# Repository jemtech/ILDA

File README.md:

# ILDA
This project is a DAC ([digital to analog converter](https://en.wikipedia.org/wiki/Digital-to-analog_converter)) which generates six [differential signals](https://en.wikipedia.org/wiki/Differential_signaling) based on the ILDA ([International Laser Display Association](http://www.laserist.org/)) [ISP-DB25 standard](http://www.laserist.org/StandardsDocs/ILDA_ISP99_rev002.pdf).
Two signals for the X and Y axis (-10V to +10V), four signals for the channels red, green and blue and one custom colour (0V to +5V).
The DAC is controlled via [SPI](https://en.wikipedia.org/wiki/Serial_Peripheral_Interface_Bus). In this case the software is written for a "Raspberry Pi", but any other controller can be used.

This project contains two sections:

1. Hardware: In this section you find a 16bit 6ch DAC for ILDA. Reaching 22kpps (measured with [ILDA Test Pattern](http://www.laserist.org/StandardsDocs/ILDA_TestPattern95_rev002.pdf), theoretical up to 400kpps) limited by the controling "Raspberry Pi". It is resulting in a resolution of 4294967296 positions (~4295 megapixels).
The asynchronous LDAC update pin at the DAC, immediately updates the DAC register with the contents of the input register, so all outputs change at the same time and can be synchronised with an external clock.
2. Software: C based software to control the ILDA-DAC with a "Raspberry Pi". Supports all Files based on the [ILDA Image Data Transfer Format](http://www.laserist.org/StandardsDocs/ILDA_IDTF14_rev011.pdf).

## Hardware
The hardware is designed with [KiCad](http://kicad.org/).
"ILDA/hardware/kicad/"
Using 5 channels (x,y,r,g,b) with 16bit at 50MHz SPI speed the DAC reaches theoretically 400kpps (50000KHz ÷ (5×24bit) = 416kpps).

## Software
### Dependencies
[Wiring Pi](http://wiringpi.com/).
### Installation
1. Install "Wiring Pi". Then follow the instructions on [Wiring Pi](http://wiringpi.com/).
2. Download this project to your "Raspberry Pi".
3. Change to the "ILDA/software/raspberrypi/" folder.
4. Run "make".

Now you can run the software with "sudo ./ildaNode".

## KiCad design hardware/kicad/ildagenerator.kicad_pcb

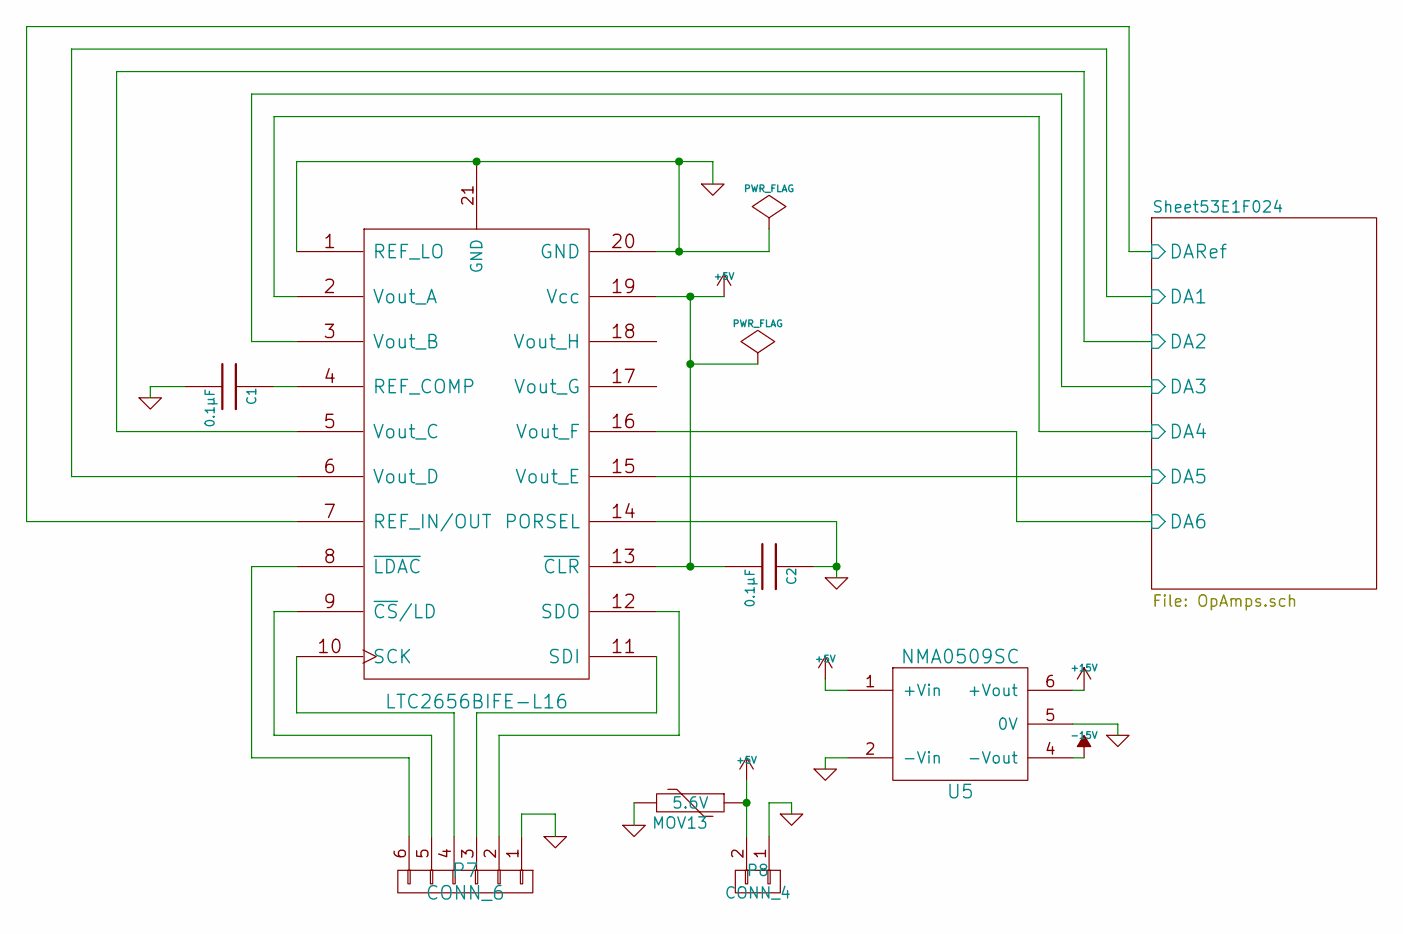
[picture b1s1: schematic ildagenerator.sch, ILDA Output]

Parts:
C1, C2: 0.1µF; C_0805_HandSoldering
MOV13: 5.6V; R_1206_HandSoldering
P7: CONN_6; Pin_Header_Straight_1x06
P8: CONN_4; Pin_Header_Straight_1x02
U1: LTC2656BIFE-L16
U5: NMA0509SC; NMA_5V_12V_15V_Series

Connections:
+5V: C2.2, MOV13.1, P8.2, U1.13 (~CLR), U1.19 (Vcc), U5.1 (+Vin)
+15V: U5.6 (+Vout); also elsewhere on the board
-15V: U5.4 (-Vout); also elsewhere on the board
/Sheet53E1F024/DA1: U1.6 (Vout_D); also elsewhere on the board
/Sheet53E1F024/DA2: U1.5 (Vout_C); also elsewhere on the board
/Sheet53E1F024/DA3: U1.3 (Vout_B); also elsewhere on the board
/Sheet53E1F024/DA4: U1.2 (Vout_A); also elsewhere on the board
/Sheet53E1F024/DA5: U1.15 (Vout_E); also elsewhere on the board
/Sheet53E1F024/DA6: U1.16 (Vout_F); also elsewhere on the board
/Sheet53E1F024/DARef: U1.7 (REF_IN/OUT); also elsewhere on the board
GND: C1.2, C2.1, MOV13.2, P7.1, P8.1, U1.1 (REF_LO), U1.14 (PORSEL), U1.20 (GND), U1.21 (GND), U5.2 (-Vin), U5.5 (0V); also elsewhere on the board
unnamed: C1.1, U1.4 (REF_COMP)
unnamed: P7.2, U1.12 (SDO)
unnamed: P7.3, U1.11 (SDI)
unnamed: P7.4, U1.10 (SCK)
unnamed: P7.5, U1.9 (~CS~/LD)
unnamed: P7.6, U1.8 (~LDAC)

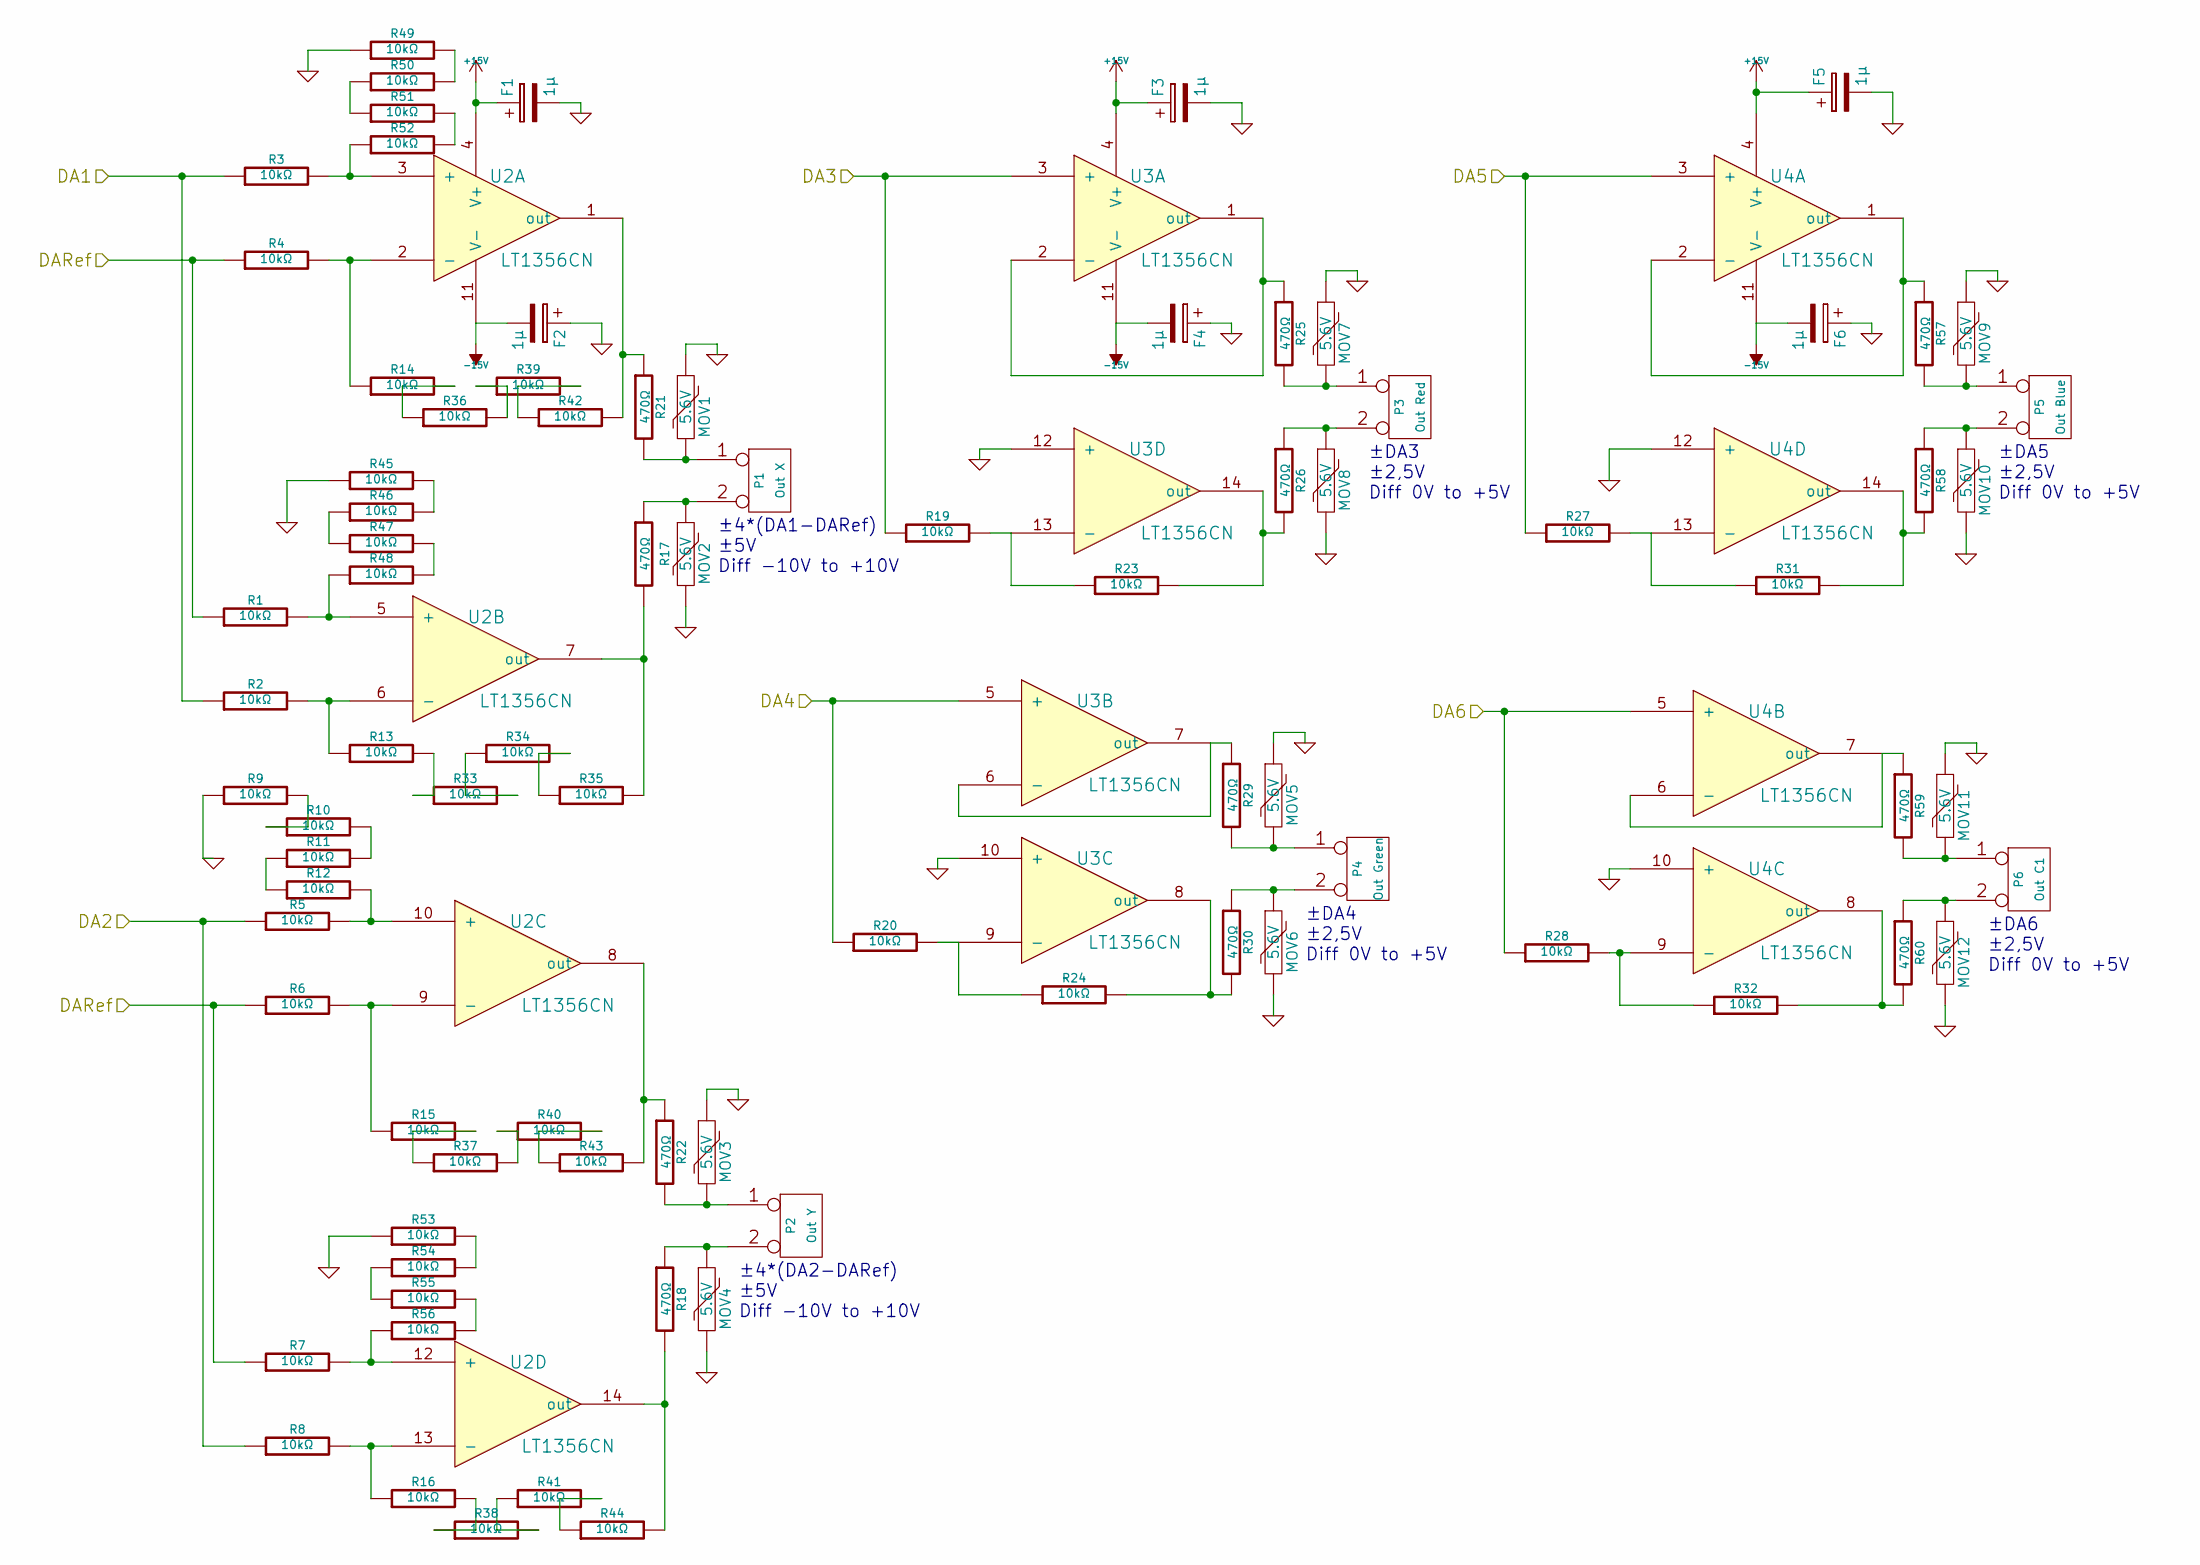
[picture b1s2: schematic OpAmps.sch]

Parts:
F1, F2, F3, F4, F5, F6: 1µ; TantalC_SizeB_EIA-3528_HandSoldering
MOV1, MOV2, MOV3, MOV4, MOV5, MOV6, MOV7, MOV8, MOV9, MOV10, MOV11, MOV12: 5.6V; R_1206_HandSoldering
P1: Out X
P2: Out Y
P3: Out Red
P4: Out Green
P5: Out Blue
P6: Out C1
R1, R2, R3, R4, R5, R6, R7, R8, R9, R10, R11, R12, R13, R14, R15, R16, R20, R24, R33, R34, R35, R36, R37, R38, R39, R40, R41, R42, R43, R44, R45, R46, R47, R48, R49, R50, R51, R52, R53, R54, R55, R56: 10kΩ; R_0603_HandSoldering
R17, R18, R21, R22: 470Ω; R_0603_HandSoldering
R19, R23, R27, R28, R31, R32: 10kΩ
R25, R26, R29, R30, R57, R58, R59, R60: 470Ω
U2, U3, U4: LT1356CN

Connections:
+15V: F1.1, F3.1, F5.1, U2.4 (V+), U3.4 (V+), U4.4 (V+); also elsewhere on the board
-15V: F2.2, F4.2, F6.2, U2.11 (V-), U3.11 (V-), U4.11 (V-); also elsewhere on the board
/Sheet53E1F024/DA1: R2.1, R3.1; also elsewhere on the board
/Sheet53E1F024/DA2: R5.1, R8.1; also elsewhere on the board
/Sheet53E1F024/DA3: R19.1, U3.3 (+); also elsewhere on the board
/Sheet53E1F024/DA4: R20.1, U3.5 (+); also elsewhere on the board
/Sheet53E1F024/DA5: R27.1, U4.3 (+); also elsewhere on the board
/Sheet53E1F024/DA6: R28.1, U4.5 (+); also elsewhere on the board
/Sheet53E1F024/DARef: R1.1, R4.1, R6.1, R7.1; also elsewhere on the board
GND: F1.2, F2.1, F3.2, F4.1, F5.2, F6.1, MOV1.1, MOV2.2, MOV3.1, MOV4.2, MOV5.1, MOV6.2, MOV7.1, MOV8.2, MOV9.1, MOV10.2, MOV11.1, MOV12.2, R9.1, R45.1, R49.1, R53.1, U3.10 (+), U3.12 (+), U4.10 (+), U4.12 (+); also elsewhere on the board
unnamed: MOV1.2, P1.1, R21.2
unnamed: MOV2.1, P1.2 (PM), R17.1
unnamed: MOV3.2, P2.1, R22.2
unnamed: MOV4.1, P2.2 (PM), R18.1
unnamed: MOV5.2, P4.1, R29.2
unnamed: MOV6.1, P4.2 (PM), R30.1
unnamed: MOV7.2, P3.1, R25.2
unnamed: MOV8.1, P3.2 (PM), R26.1
unnamed: MOV9.2, P5.1, R57.2
unnamed: MOV10.1, P5.2 (PM), R58.1
unnamed: MOV11.2, P6.1, R59.2
unnamed: MOV12.1, P6.2 (PM), R60.1
unnamed: R1.2, R48.1, U2.5 (+)
unnamed: R3.2, R52.1, U2.3 (+)
unnamed: R9.2, R10.1
unnamed: R10.2, R11.2
unnamed: R11.1, R12.1
unnamed: R5.2, R12.2, U2.10 (+)
unnamed: R2.2, R13.1, U2.6 (-)
unnamed: R13.2, R33.1
unnamed: R4.2, R14.1, U2.2 (-)
unnamed: R14.2, R36.1
unnamed: R6.2, R15.1, U2.9 (-)
unnamed: R15.2, R37.1
unnamed: R8.2, R16.1, U2.13 (-)
unnamed: R16.2, R38.1
unnamed: R17.2, R35.2, U2.7 (out)
unnamed: R18.2, R44.2, U2.14 (out)
unnamed: R19.2, R23.1, U3.13 (-)
unnamed: R20.2, R24.1, U3.9 (-)
unnamed: R21.1, R42.2, U2.1 (out)
unnamed: R22.1, R43.2, U2.8 (out)
unnamed: R23.2, R26.2, U3.14 (out)
unnamed: R24.2, R30.2, U3.8 (out)
unnamed: R25.1, U3.1 (out), U3.2 (-)
unnamed: R27.2, R31.1, U4.13 (-)
unnamed: R28.2, R32.1, U4.9 (-)
unnamed: R29.1, U3.6 (-), U3.7 (out)
unnamed: R31.2, R58.2, U4.14 (out)
unnamed: R32.2, R60.2, U4.8 (out)
unnamed: R33.2, R34.1
unnamed: R34.2, R35.1
unnamed: R36.2, R39.1
unnamed: R37.2, R40.1
unnamed: R38.2, R41.1
unnamed: R39.2, R42.1
unnamed: R40.2, R43.1
unnamed: R41.2, R44.1
unnamed: R45.2, R46.2
unnamed: R46.1, R47.1
unnamed: R47.2, R48.2
unnamed: R49.2, R50.2
unnamed: R50.1, R51.1
unnamed: R51.2, R52.2
unnamed: R53.2, R54.2
unnamed: R54.1, R55.1
unnamed: R55.2, R56.2
unnamed: R7.2, R56.1, U2.12 (+)
unnamed: R57.1, U4.1 (out), U4.2 (-)
unnamed: R59.1, U4.6 (-), U4.7 (out)

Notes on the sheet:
±4*(DA1-DARef) ±5V Diff -10V to +10V
±4*(DA2-DARef) ±5V Diff -10V to +10V
±DA3 ±2,5V Diff 0V to +5V
±DA4 ±2,5V Diff 0V to +5V
±DA5 ±2,5V Diff 0V to +5V
±DA6 ±2,5V Diff 0V to +5V

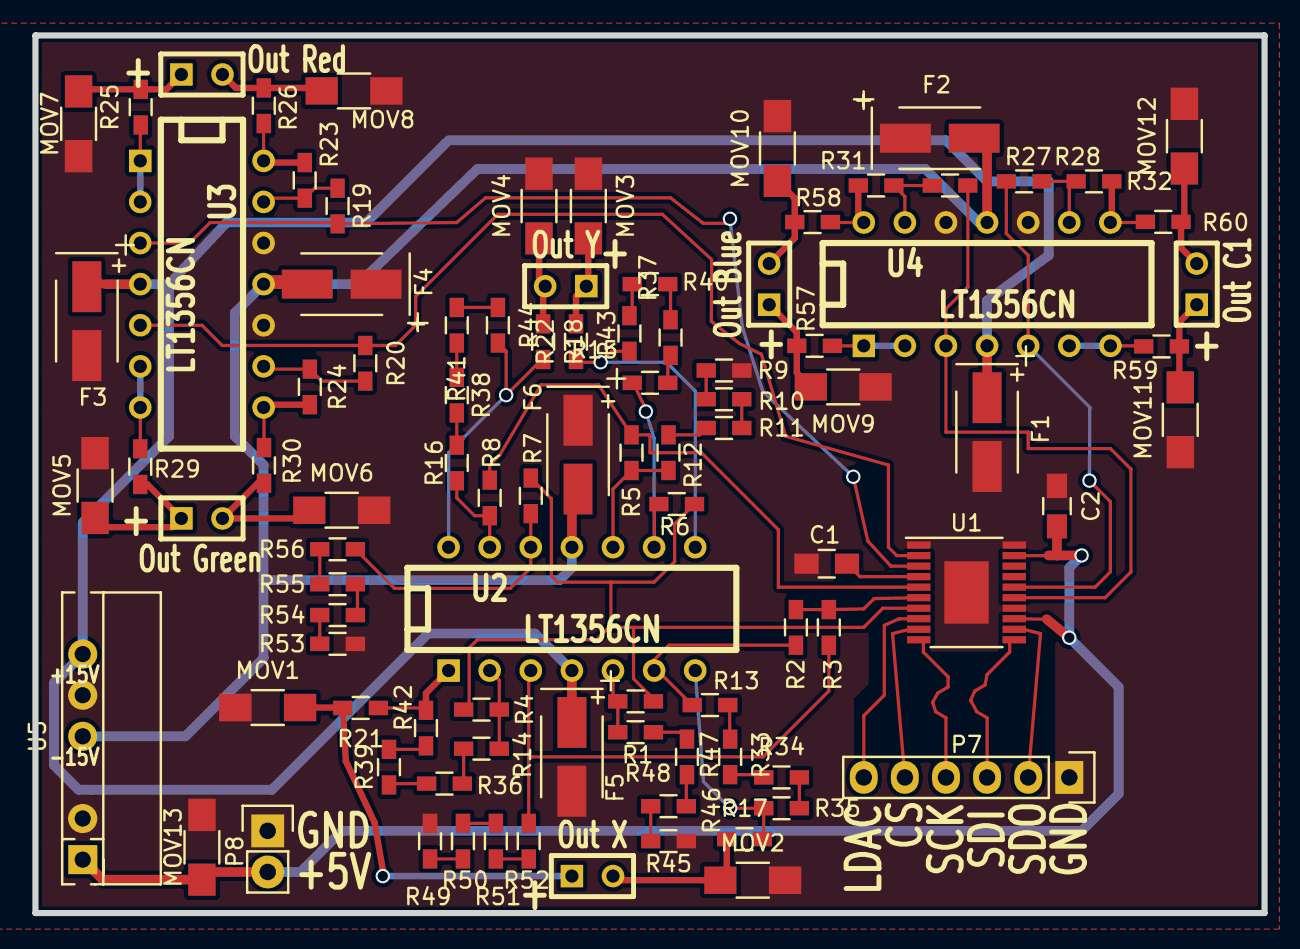
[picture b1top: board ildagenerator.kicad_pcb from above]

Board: 2 copper layers, 75.9 x 54.2 mm, 94 parts (0 on the bottom side), 77 nets.

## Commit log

2015-08-25 hardware init
2015-08-25 software init
2015-08-26 value conversion
2015-08-26 software improved
2015-08-26 remove bug and add makefile
2015-08-27 add output protection
2015-08-27 rout output protection
2015-08-28 beginn with file reader
2015-08-28 mov output protect
2015-08-29 placing movs
2015-08-29 better Readme
2015-08-29 typo correction
2015-08-29 documentation
2015-08-31 add a menue
2015-08-31 switch menue item
2015-08-31 onboard power dc/dc
2015-08-31 clean
2015-08-31 correct socket
2015-09-04 add ILDA file support
2015-09-05 add options, increase speed to 22kpps
2015-09-05 update readme with new speed
2015-09-06 better reading performance
2021-11-08 Update README.md
    https://forum.kicad.info/t/warning-avoid-all-links-to-kicad-pcb-org-use-kicad-org/31521
